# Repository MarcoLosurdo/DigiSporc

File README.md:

# DigiSporc

> The simple and cheap parody of Digispark

DigiSporc is a mini single-board microcontroller for ATtiny25/45/85 family that is **really easy to program and use** thanks to the application of a simple idea:

*its connector, plugged in the first female strip connector  of an Arduino Uno or Duemilanove (from the AREF to the digital port 8), has the pin already arranged in the right sequence to be able to be programmed with an Arduino in ISP mode.*

## 1.Intro
A few weeks ago, on Kickstarter, I saw a very interesting project called [Digispark](http://www.kickstarter.com/projects/digistump/digispark-the-tiny-arduino-enabled-usb-dev-board).

> Digispark - The micro-sized, Arduino enabled, usb development board

I'm not an electronic engineer, I just know a bit as the Arduino boards (and clones) works, so the first question I did was: «All the Arduino needs an FTDI chip; how is possible to program an ATtiny directly through a USB?».   
It seems that the "magic" happens thanks to a special bootloader and a data transmission technique called [bitbanging](http://en.wikipedia.org/wiki/Bit_banging). All this at the beginning it seemed very cool... but too unnecessarily complicated for someone like me who barely knows the difference between a LED and a capacitor.

Then, I remembered a [simple tutorial](http://hlt.media.mit.edu/?p=1695) published by the _MIT media lab_ about ATtiny programming using an Arduino. Giving it a further look I noticed that all pins required to program an ATtiny were on the strip connector Arduino that goes from AREF to digital 8, furthermore, the pins of a ATtiny are exactly eight as on that strip.  
So I came up with an idea: **why don't build an ATtiny45/85 board that can be plugged into an Arduino connector?**

Nothing could be easier! Et voilà:

That pic shows two prototypes (with and without the reset button). Into the repository you can find both named **DigiSporc** and **DigiSporc_Nano** (yes, I'm a sarcastic Apple fanboy).  
The prototype of DigiSporc in that pic, however, has no voltage regulator.

### 1.1.ATtiny and DigiSpork Pin-Outs

## 2.Getting Started
This is the DigiSporc Nano ([schematics](https://raw.github.com/MarcoLosurdo/DigiSporc/master/DigiSporc_nano.png)):  
  
and all you need to build it is:

### 2.1.Hardware
* 1x 10K resistor (brown, black, orange, gold)
* 1x 1K resistor (brown, black, red, gold)
* 2x 0.1uF capacitors (but just one of them will be welded on the board, I promise!)
* 1x ATtiny85 (or 45)
* 1x 3mm LED
* 1x 1x8 pin headers (90° or straight)
* 1x 8x8 matrix board (but also an 8x6 is enough)

It is always better to avoid solder directly to a microcontroller, and I prefer to use two 1x4 female pin header instead a socket.
Into the schematic there is a place for another 1x2 female pin but you'll need it if you plan to use the original version of ArduinoISP.

This tutorial was written by an Italian, so do not expect too many details (much less a perfect grammar). I'm not lazy, just don't wanna offend your intelligence: it is obvious that in order to complete the project you will need a **soldering iron**, some **tin wire**, an **Arduino** (Duemilanove or Uno) and an **USB cable** too. 
 
If you have no idea how to read a schematic or to make a circuit on a matrix board: search on Google. The internet is full of tinkering tutorials and I do not want to add another one.
 
...Ok, I'm lazy. Do your best, I trust you!

### 2.2.Software
* [Arduino IDE](http://arduino.cc/en/Main/Software).
* My version of [ArduinoISP](https://raw.github.com/MarcoLosurdo/DigiSporc/master/ArduinoISP_per_DigiSporc.ino)
* [ATtiny hardware support](https://github.com/damellis/attiny/archive/master.zip)

#### 2.2.1.Installing ATtiny support in 37 easy steps:
1. Locate your Arduino sketchbook folder (start **Arduino IDE** and watch in the preferences);
1. if non exists, create a new sub-folder **hardware** in the sketchbook folder;
1. copy the attiny folder from inside the .zip to the **hardware** folder (you should obtain a structure like _Documents/Arduino/hardware/attiny_ that contains the file **boards.txt** and another folder called variants);
1. restart the Arduino IDE;
1. you should see ATtiny entries in the _Tools > Board_ menu;
1. the steps are just 5, not 37. I was joking. Move on.

### 2.3.ATtiny setup
1. Connect and select your Arduino from _Tools > Boards_ menu (e.g. **Arduino Uno**) and the right serial port (if you have a problem already at this step, please refer to the [official Arduino IDE guide](http://arduino.cc/en/Guide/HomePage));
1. connect and upload [ArduinoISP per DigiSporc](https://raw.github.com/MarcoLosurdo/DigiSporc/master/ArduinoISP_per_DigiSporc.ino) onto your Arduino board;
1. select your DigiSporc microcontroller from the _Tools > Boards_ menu (e.g. **ATtiny85 8 MHz**);

1. Select **Arduino as ISP** from the _Tools > Programmer_ menu;  

1. plug a 0.1uF **ceramic** capacitor between Arduino's RESET and GND (sometimes it is unnecessary, but it is always better to do);  
  
You can also use a electrolytic capacitor (10uF), but you have to make sure to plug the negative pin of capacitor (shorter and marked with a black stripe on the case of the capacitor) onto GND.

1. plug your DigiSporc into the AREF–DIGITAL8 slot;  

1. run the **Burn Bootloader** command from the Tools menu.  

You need to do this **once** for every ATtiny.  
This doesn’t burn a bootloader onto the ATtiny, just configures the fuse bits of the microcontroller so it runs at 8 MHz.

### 2.4.Programming the DigiSporc for the first time
If you've restarted the Arduino IDE or changed something, repeat the steps from 1 to 6 as above for the ATtiny setup, then:

1. Open the **Blink** sketch from the _File > Examples > Basics_ menu;
1. edit the sketch and change the pin numbers from 13 to 0;  
`int led = 13;` → `int led = 0;`
1. upload the sketch and enjoy your blinking LED (if the LED don't blinks, something gone wrong).

## 3.Notes
* On the Arduino used as ISP programmer, still possible to run  the original version (supplied with the Arduino IDE) of **Arduino ISP**. But will be necessary to manually perform the connection between the 5V pin of Arduino and DigiSporc to provide the power supply;
* DigiSporc footprint it's 36,84% (175mm^2) less than the best competitor:
 
* OK, the DigiSpark seems to have 6 I/O pin and Digisporc just 5. But remember: less is more! :-?
* **sporc** it's the abbreviation of the italian word "sporco" (dirty).
* **I want to clarify explicitly**: The fact that the DigiSporc really works, does not mean that this is a serious project. I just wanted to do something to practice in the use of Github, EagleCad, Markdown and teasing (just a little) who use Kickstarter to raise money for projects that, in reality, are nothing more than other open source projects combined toghether.

## 4.Credits
- The project is based on the tutorial [Programming an ATtiny w/ Arduino 1.0.1](http://hlt.media.mit.edu/?p=1695) by MIT media lab.
- Many thanks to the people of [Tokyo Hackerspace](http://tokyohackerspace.org/) for any advices, but especially for the unexpected enthusiasm with which they welcomed the project.
- I’m sorry not to be able to thank guys DigiSpark, but at the time of publication of my project on Github, they had not yet published nothing of their "open hardware" board… probably, they were too busy to collect their quarter of a million dollars on KickStarter :D #LOL

## 5.Licence
DigiSporc (c) 2012, Marco Losurdo  
This project is realeased under the [CC-BY-SA 3.0](http://creativecommons.org/licenses/by-sa/3.0/us/) License.

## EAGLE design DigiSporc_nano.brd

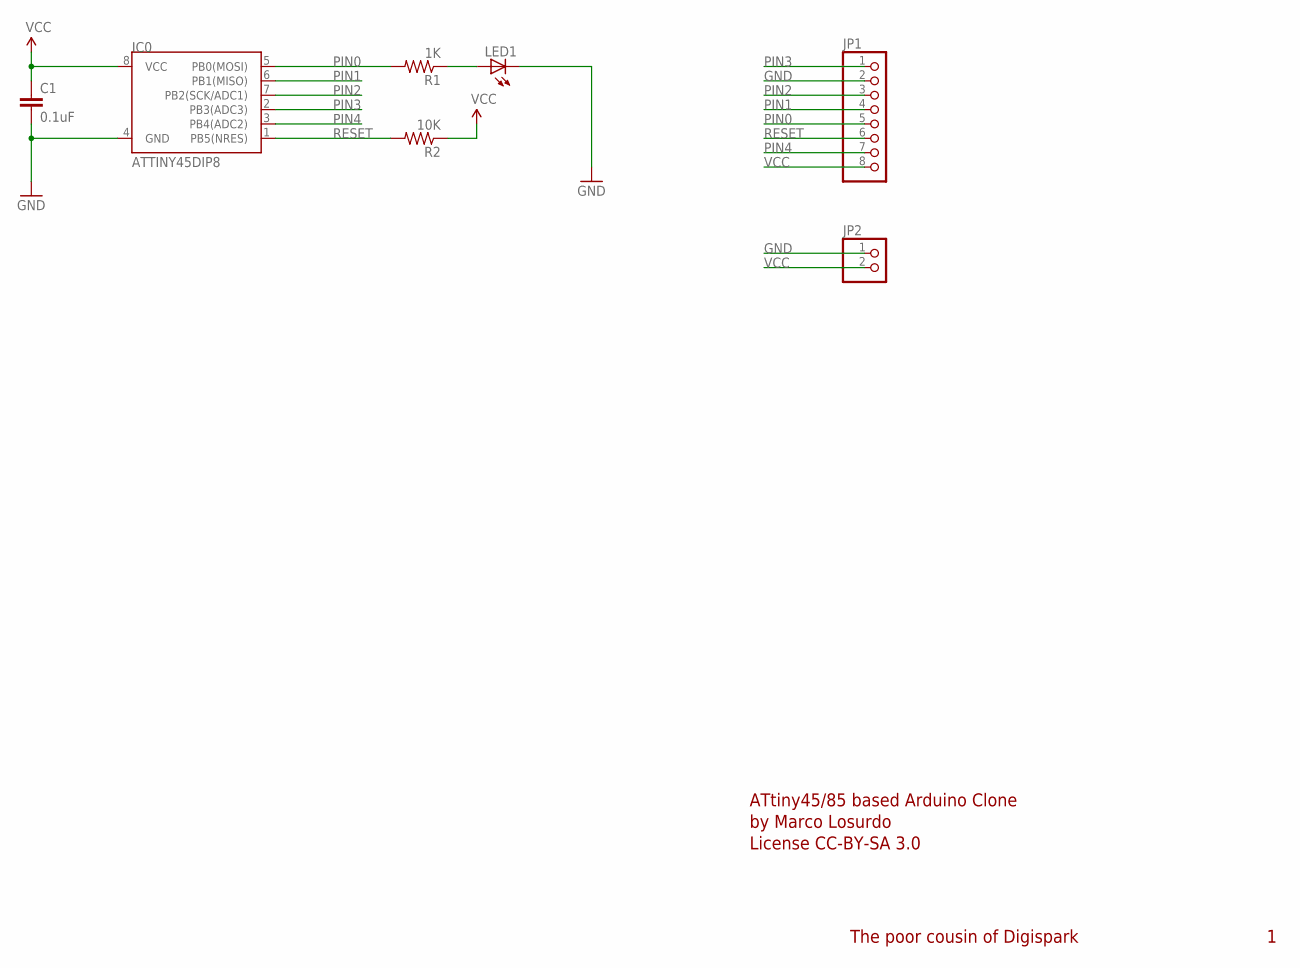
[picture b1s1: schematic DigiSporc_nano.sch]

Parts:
C1: 0.1uF; CAP-PTH-SMALL
IC0: ATTINY45DIP8; DIP08
JP1: PINHD-1X8; 1X08
JP2: PINHD-1X2; 1X02
LED1: LED3MM
R1: 1K; 0204/7
R2: 10K; 0204/7

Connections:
GND: C1.2, IC0.4 (GND), JP1.2, JP2.1, LED1.K (C)
unnamed: LED1.A, R1.1
PIN0: IC0.5 (PB0(MOSI)), JP1.5, R1.2
PIN1: IC0.6 (PB1(MISO)), JP1.4
PIN2: IC0.7 (PB2(SCK/ADC1)), JP1.3
PIN3: IC0.2 (PB3(ADC3)), JP1.1
PIN4: IC0.3 (PB4(ADC2)), JP1.7
RESET: IC0.1 (PB5(NRES)), JP1.6, R2.2
VCC: C1.1, IC0.8 (VCC), JP1.8, JP2.2, R2.1

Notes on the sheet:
ATtiny45/85 based Arduino Clone
by Marco Losurdo
License CC-BY-SA 3.0
The poor cousin of Digispark

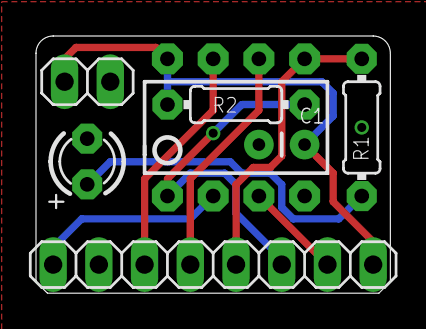
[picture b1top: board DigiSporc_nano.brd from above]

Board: 2 copper layers, 19.7 x 14.3 mm, 8 parts (1 on the bottom side), 9 nets.

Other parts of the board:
U$1: OSHWLOGO_TOL_0.2

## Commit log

2012-09-06 README file in (wannabe) english.
2012-09-06 Readme update.
2012-09-07 Comments and warning added
2012-09-07 README update
2012-09-07 Photo folder
2012-09-08 organizing folders...
2012-09-08 new proto pic
2012-09-08 New Pic
2012-09-08 Pic added
2012-09-08 Other pics...
2012-09-08 pics...
2012-09-08 Pic componenti
2012-09-08 Pic Update
2012-09-08 Ho aggiunto il maiale!
2012-09-08 Readme v.1.0
2012-09-09 Schematics and board in .png added
2012-09-13 New Dir
2012-09-19 Heartbeat parameters changed.
    Heartbeat parameters changed.
    It is just a cosmetic change for the LED blinking, that don't affect
    any practical feature.
2013-03-08 Link Update
    Aggiornato link ad hardware support per ATtiny.
